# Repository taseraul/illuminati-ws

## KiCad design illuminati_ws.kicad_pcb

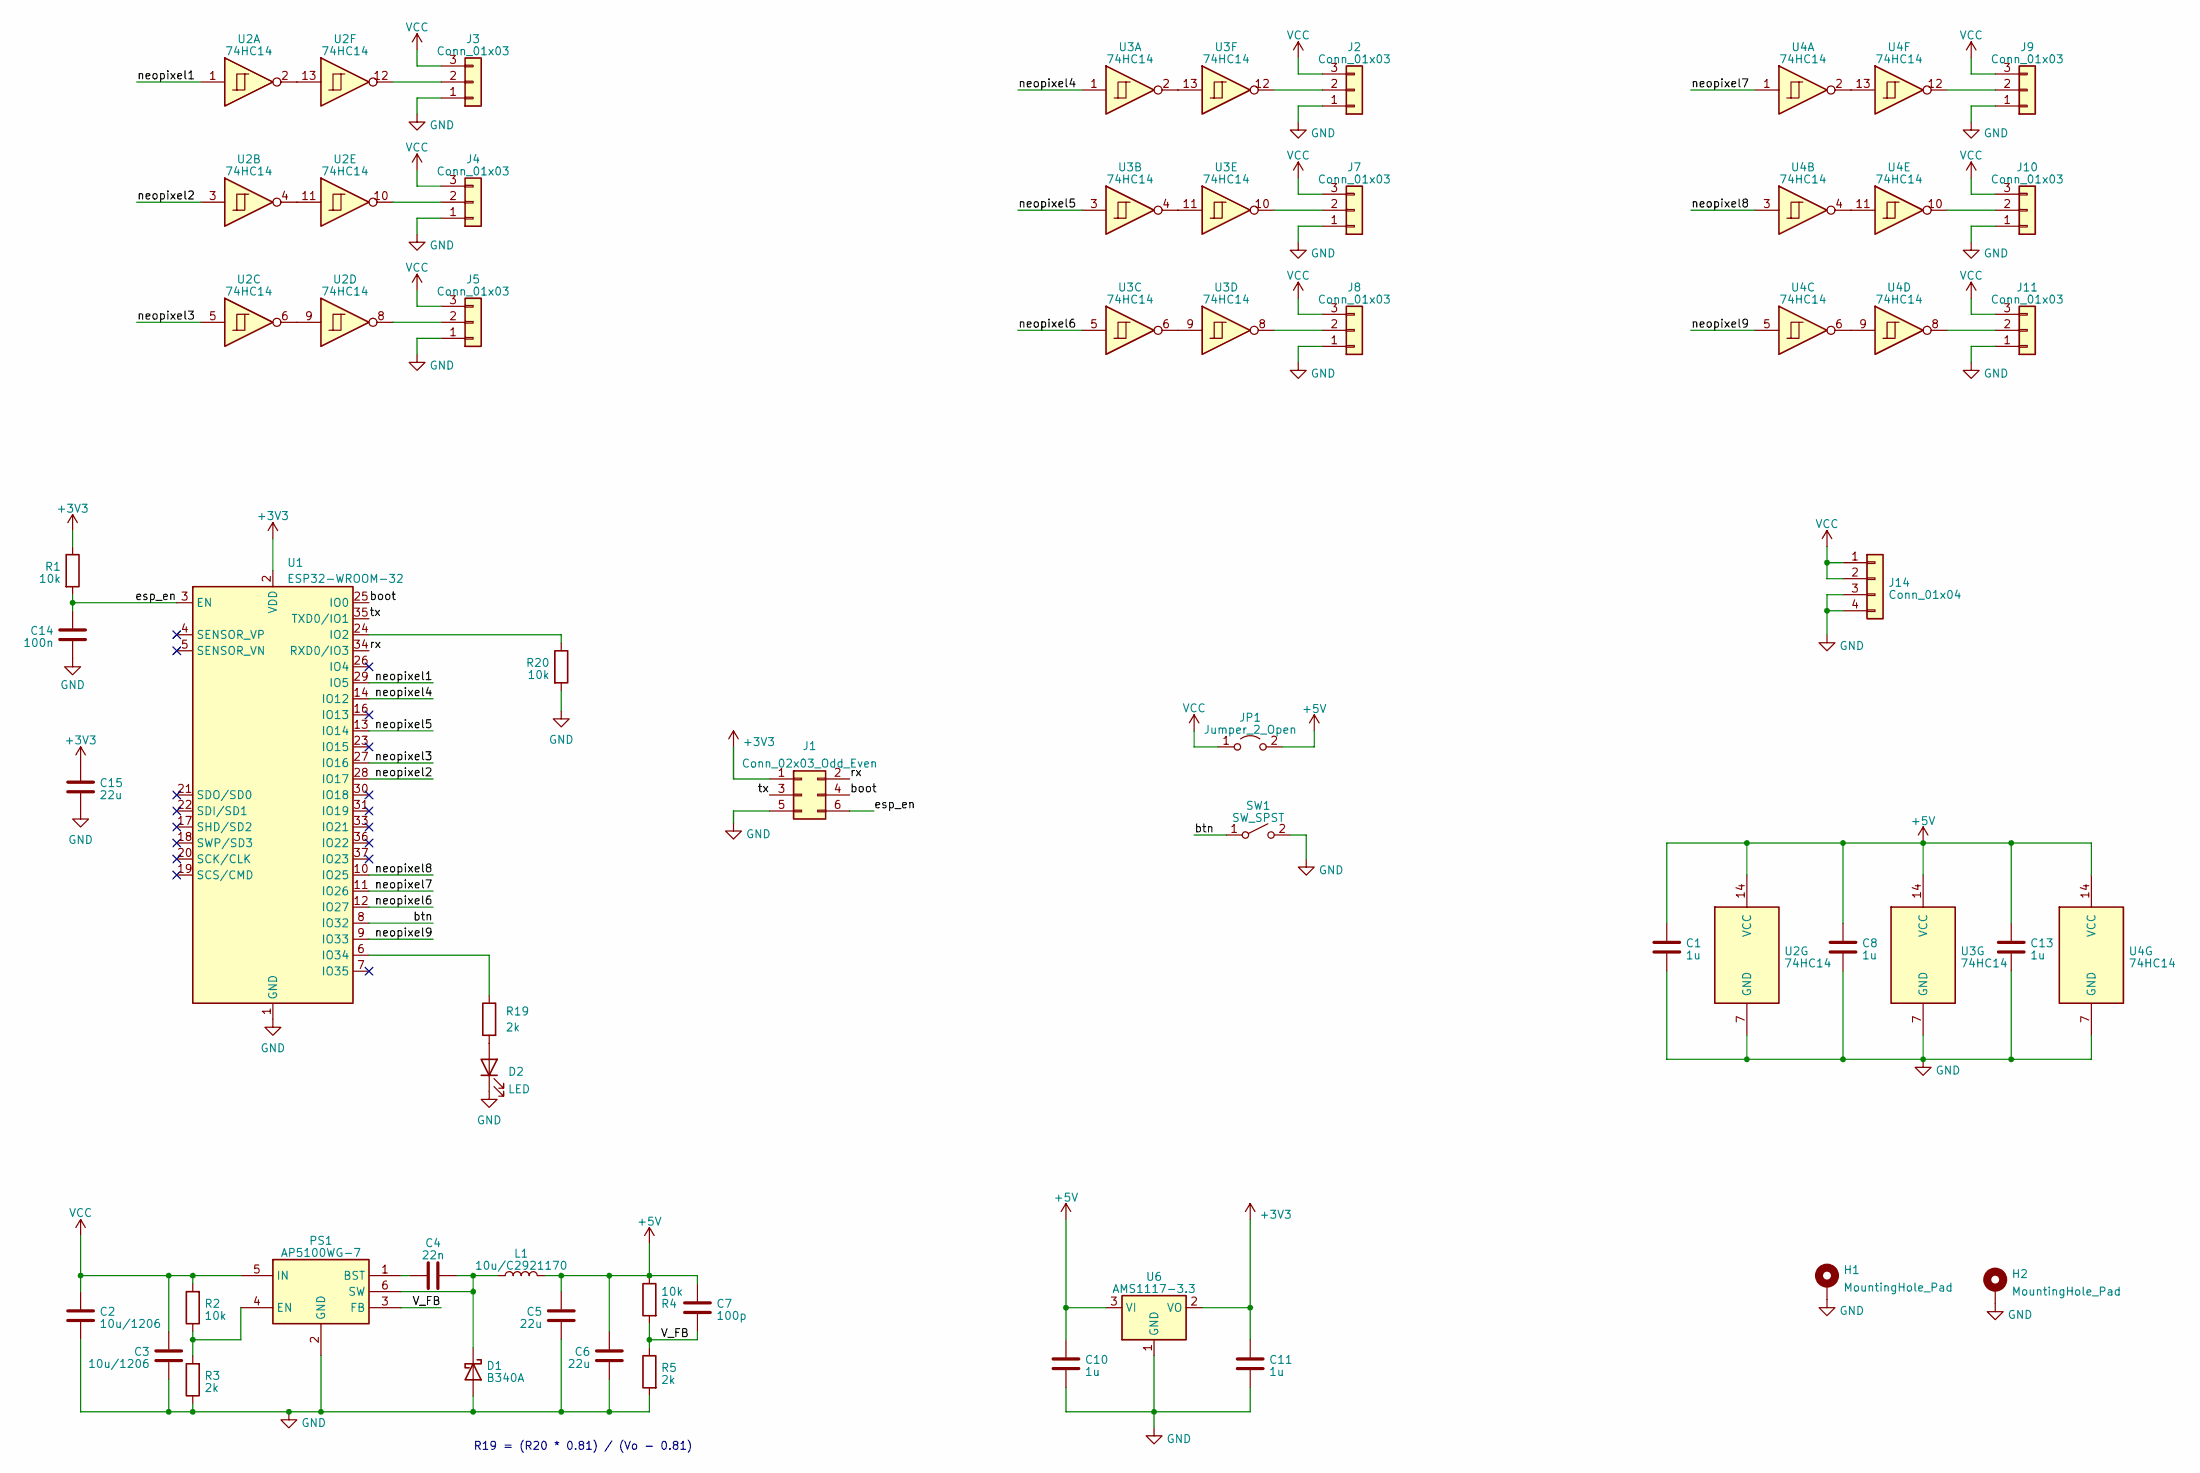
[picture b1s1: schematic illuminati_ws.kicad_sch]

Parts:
C1, C8, C10, C11, C13: 1u; C_0805_2012Metric; MPN C28323
C2, C3: 10u/1206; C_1206_3216Metric; MPN C13585
C4: 22n; C_0603_1608Metric; MPN C21122
C5, C6, C15: 22u; C_0805_2012Metric; MPN C45783
C7: 100p; C_0603_1608Metric; MPN C1790
C14: 100n; C_0603_1608Metric; MPN C14663
D1: B340A; D_SMA; MPN C3018525
D2: LED; LED_0805_2012Metric; MPN C34499
H1, H2: MountingHole_Pad; MountingHole_3.2mm_M3_DIN965_Pad
J1: Conn_02x03_Odd_Even; PinHeader_2x03_P2.54mm_Vertical
J2, J3, J4, J5, J7, J8, J9, J10, J11: Conn_01x03; TerminalBlock_Phoenix_MKDS-1,5-3_1x03_P5.00mm_Horizontal; MPN C8401
J14: Conn_01x04; TerminalBlock_Phoenix_MKDS-1,5-4_1x04_P5.00mm_Horizontal; MPN C192769
JP1: Jumper_2_Open; SolderJumper-2_P1.3mm_Open_TrianglePad1.0x1.5mm
L1: 10u/C2921170; L_Chilisin_BMRA00040420; MPN C2921170
PS1: AP5100WG-7; SOT95P285X140-6N; Mouser Part Number 621-AP5100WG-7
R1, R2, R4, R20: 10k; R_0603_1608Metric; MPN C25804
R3, R5, R19: 2k; R_0603_1608Metric; MPN C22975
SW1: SW_SPST; SW_PUSH_6mm_H5mm
U1: ESP32-WROOM-32
U2, U3, U4: 74HC14; SOIC-14_3.9x8.7mm_P1.27mm; MPN C5967
U6: AMS1117-3.3; SOT-223-3_TabPin2; MPN C6186

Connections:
+3V3: C11.1, C15.1, J1.1, R1.1, U1.2 (VDD), U6.2 (VO)
+5V: C1.1, C5.1, C6.1, C7.1, C8.1, C10.1, C13.1, JP1.2 (B), L1.2, R4.1, U2.14 (VCC), U3.14 (VCC), U4.14 (VCC), U6.3 (VI)
/V_FB: C7.2, PS1.3 (FB), R4.2, R5.1
/boot: J1.4, U1.25 (IO0)
/btn: SW1.1 (A), U1.8 (IO32)
/esp_en: C14.1, J1.6, R1.2, U1.3 (EN)
/neopixel1: U1.29 (IO5), U2.1
/neopixel2: U1.28 (IO17), U2.3
/neopixel3: U1.27 (IO16), U2.5
/neopixel4: U1.14 (IO12), U3.1
/neopixel5: U1.13 (IO14), U3.3
/neopixel6: U1.12 (IO27), U3.5
/neopixel7: U1.11 (IO26), U4.1
/neopixel8: U1.10 (IO25), U4.3
/neopixel9: U1.9 (IO33), U4.5
/rx: J1.2, U1.34 (RXD0/IO3)
/tx: J1.3, U1.35 (TXD0/IO1)
GND: C1.2, C2.2, C3.2, C5.2, C6.2, C8.2, C10.2, C11.2, C13.2, C14.2, C15.2, D1.2 (A), D2.1 (K), H1.1, H2.1, J1.5, J2.1, J3.1, J4.1, J5.1, J7.1, J8.1, J9.1, J10.1, J11.1, J14.3, J14.4, PS1.2 (GND), R3.1, R5.2, R20.2, SW1.2 (B), U1.1 (GND), U1.15 (GND), U1.38 (GND), U1.39 (GND), U2.7 (GND), U3.7 (GND), U4.7 (GND), U6.1 (GND)
unnamed: C4.2, D1.1 (K), L1.1, PS1.6 (SW)
unnamed: D2.2 (A), R19.2
unnamed: J2.2, U3.12
unnamed: J3.2, U2.12
unnamed: J4.2, U2.10
unnamed: J5.2, U2.8
unnamed: J7.2, U3.10
unnamed: J8.2, U3.8
unnamed: J9.2, U4.12
unnamed: J10.2, U4.10
unnamed: J11.2, U4.8
unnamed: C4.1, PS1.1 (BST)
unnamed: PS1.4 (EN), R2.1, R3.2
unnamed: R20.1, U1.24 (IO2)
unnamed: R19.1, U1.6 (IO34)
unnamed: U2.6, U2.9
unnamed: U2.4, U2.11
unnamed: U2.2, U2.13
unnamed: U3.6, U3.9
unnamed: U3.4, U3.11
unnamed: U3.2, U3.13
unnamed: U4.6, U4.9
unnamed: U4.4, U4.11
unnamed: U4.2, U4.13
VCC: C2.1, C3.1, J2.3, J3.3, J4.3, J5.3, J7.3, J8.3, J9.3, J10.3, J11.3, J14.1, J14.2, JP1.1 (A), PS1.5 (IN), R2.2

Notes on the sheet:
R19 = (R20 * 0.81) / (Vo - 0.81)

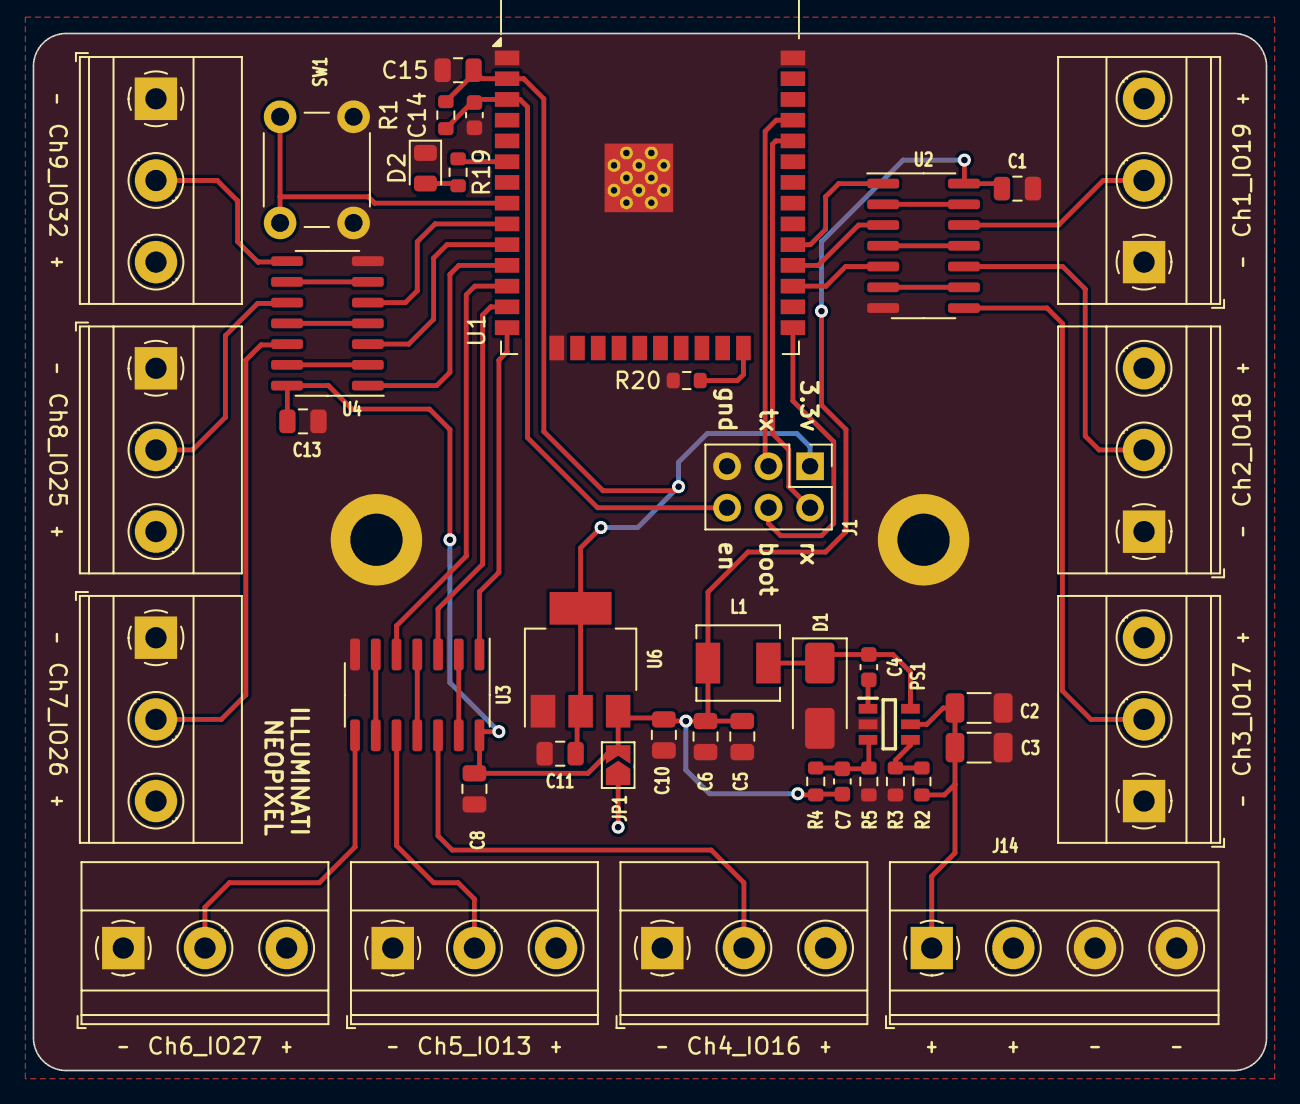
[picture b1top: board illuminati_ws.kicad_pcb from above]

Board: 2 copper layers, 75.5 x 63.5 mm, 44 parts (0 on the bottom side), 43 nets.

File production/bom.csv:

Designator,Footprint,Quantity,Value,LCSC Part #
"C1, C10, C11, C13, C8",0805,5,1u,C28323
C14,0603,1,100n,C14663
"C15, C5, C6",0805,3,22u,C45783
"C2, C3",1206,2,10u/1206,C13585
C4,0603,1,22n,C21122
C7,0603,1,100p,C1790
D1,D_SMA,1,B340A,C3018525
D2,0805,1,LED,C34499
"H1, H2",MountingHole_3.2mm_M3_DIN965_Pad,2,MountingHole_Pad,
J1,PinHeader_2x03_P2.54mm_Vertical,1,Conn_02x03_Odd_Even,
"J10, J11, J2, J3, J4, J5, J7, J8, J9","TerminalBlock_Phoenix_MKDS-1,5-3_1x03_P5.00mm_Horizontal",9,Conn_01x03,C8401
J14,"TerminalBlock_Phoenix_MKDS-1,5-4_1x04_P5.00mm_Horizontal",1,Conn_01x04,C192769
JP1,SolderJumper-2_P1.3mm_Open_TrianglePad1.0x1.5mm,1,Jumper_2_Open,
L1,L_Chilisin_BMRA00040420,1,10u/C2921170,C2921170
PS1,SOT95P285X140-6N,1,AP5100WG-7,C114647
"R1, R2, R20, R4",0603,4,10k,C25804
"R19, R3, R5",0603,3,2k,C22975
SW1,SW_PUSH_6mm_H5mm,1,SW_SPST,
U1,ESP32-WROOM-32,1,ESP32-WROOM-32,
"U2, U3, U4",SOIC-14_3.9x8.7mm_P1.27mm,3,74HC14,C5967
U6,SOT-223-3_TabPin2,1,AMS1117-3.3,C6186

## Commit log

2024-07-08 Board V2 swap esp32c3 for esp32
